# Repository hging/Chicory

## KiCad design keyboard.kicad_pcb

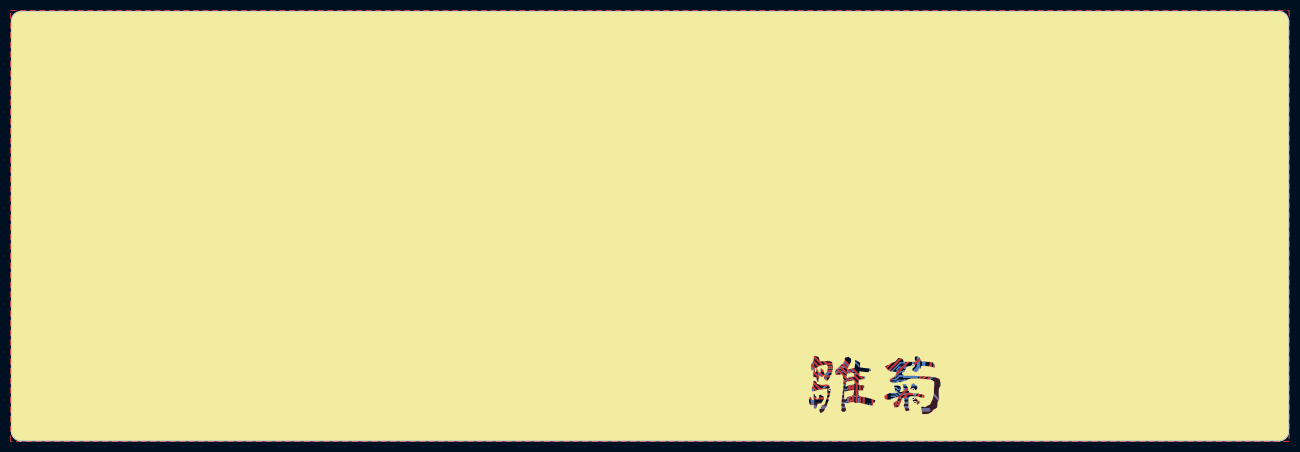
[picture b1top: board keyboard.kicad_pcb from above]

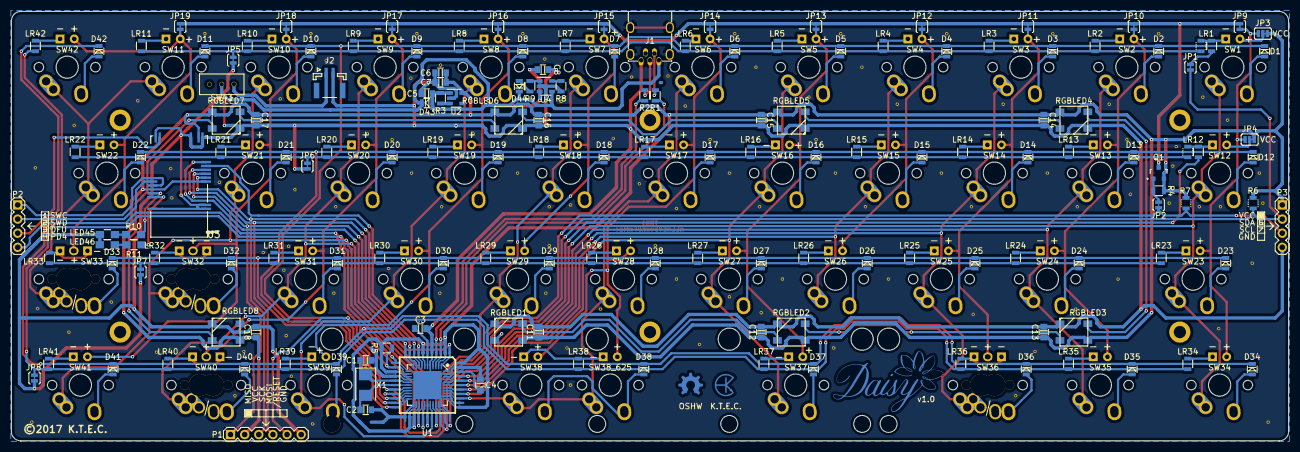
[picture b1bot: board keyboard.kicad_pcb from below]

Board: 2 copper layers, 229.6 x 77.2 mm, 349 parts (159 on the bottom side), 162 nets.

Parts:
C1, C2: 22pF; C_0805
C3: 1uF; C_0805
C4, C11, C12, C13, C14, C15, C16, C17, C18: 100nF; C_0805
C5, C6, C7, C8: 10uf; C_0805
D1, D2, D3, D4, D5, D6, D7, D8, D9, D10, D11, D12, D13, D14, D15, D16, D17, D18, D19, D20, D21, D22, D23, D24, D25, D26, D27, D28, D29, D30, D31, D32, D33, D34, D35, D36, D37, D38, D39, D40, D41, D42: DIODE; D_0805_V2
D43: D_Schottky_Small_ALT; D_0805_V2
D44: LED; D_0805_V2
J1: USB_MINI-B
J2: Conn_01x02; JST_GH_SM02B-GHS-TB_02x1.25mm_Angled
JP1, JP2, JP5, JP6, JP7, JP8, JP9, JP10, JP11, JP12, JP13, JP14, JP15, JP16, JP17, JP18, JP19: JUMPER; Jumper_SMD_2Pads_NC_V
JP3, JP4: JUMPER3; Jumper_SMD_3Pads_NC12
LED1, LED2, LED3, LED4, LED5, LED6, LED7, LED8, LED9, LED10, LED11, LED12, LED13, LED14, LED15, LED16, LED17, LED18, LED19, LED20, LED21, LED22, LED23, LED24, LED25, LED26, LED27, LED28, LED29, LED30, LED31, LED34, LED35, LED37, LED38, LED38_625, LED39, LED41, LED42: LED; MX1A_LED_Polar
LED32, LED33, LED36, LED40: LED; MX1A_LED_Polar_Dual
LED45, LED46: LED; R_0805_HandSoldering
LOGO1: Daisy_SilkS
LOGO2: Daisy_Logo
LOGO3: OSHW_LOGO; OSHW_Logo
LOGO4: KTEC_LOGO; KTEC_Logo
LR1, LR2, LR3, LR4, LR5, LR6, LR7, LR8, LR9, LR10, LR11, LR12, LR13, LR14, LR15, LR16, LR17, LR18, LR19, LR20, LR21, LR22, LR23, LR24, LR25, LR26, LR27, LR28, LR29, LR30, LR31, LR32, LR33, LR34, LR35, LR36, LR37, LR38, LR39, LR40, LR41, LR42: 330R; R_0805_V1
LR1-2, LR12-2: 330R; R_0805_NA
P1: ISP; Socket_Strip_Straight_1x06_Pitch2.54mm
P2: CONN_01X03; Socket_Strip_Straight_1x04_Pitch2.54mm
P3: GPIO_CLUSTER2; Socket_Strip_Straight_1x04_Pitch2.54mm
Q1: MOS_P; SOT-23
R1, R2: 22R; R_0805_V1
R3, R8: 100K; R_0805_V1
R4, R5: 10K; R_0805_V1
R6, R7: 4.7K; R_0805_NA
R9: 1K; R_0805_V1
R10, R11: 2.2K; R_0805_HandSoldering
RGBLED1, RGBLED2, RGBLED3, RGBLED4, RGBLED5, RGBLED6, RGBLED7, RGBLED8: WS2812B
SHIELD: Via_0.6mm
SHIELD#2, SHIELD#3, SHIELD#4, SHIELD#5, SHIELD#6, SHIELD#7, SHIELD#8, SHIELD#9, SHIELD#10, SHIELD#11, SHIELD#12, SHIELD#13, SHIELD#14, SHIELD#15, SHIELD#16, SHIELD#17, SHIELD#18, SHIELD#19, SHIELD#20, SHIELD#21, SHIELD#22, SHIELD#23, SHIELD#24, SHIELD#25, SHIELD#26, SHIELD#27, SHIELD#28, SHIELD#29, SHIELD#30, SHIELD#31, SHIELD#32, SHIELD#33, SHIELD#34, SHIELD#35, SHIELD#36, SHIELD#37, SHIELD#38, SHIELD#39, SHIELD#40, SHIELD#41, SHIELD#42, SHIELD#43, SHIELD#44, SHIELD#45, SHIELD#46, SHIELD#47, SHIELD#48, SHIELD#49, SHIELD#50, SHIELD#51, SHIELD#52, SHIELD#53, SHIELD#54, SHIELD#55, SHIELD#56, SHIELD#57, SHIELD#58, SHIELD#59, SHIELD#60, SHIELD#61, SHIELD#62, SHIELD#63, SHIELD#64, SHIELD#65, SHIELD#66, SHIELD#67, SHIELD#68, SHIELD#69, SHIELD#70, SHIELD#71, SHIELD#72, SHIELD#73, SHIELD#74, SHIELD#75, SHIELD#76, SHIELD#77, SHIELD#78, SHIELD#79, SHIELD#80, SHIELD#81, SHIELD#82, SHIELD#83, SHIELD#84, SHIELD#85, SHIELD#86, SHIELD#87, SHIELD#88, SHIELD#89, SHIELD#90, SHIELD#91, SHIELD#92, SHIELD#93, SHIELD#94, SHIELD#95, SHIELD#96, SHIELD#97, SHIELD#98, SHIELD#99, SHIELD#100, SHIELD#101, SHIELD#102, SHIELD#103: Via_0.6mm
SW1, SW2, SW3, SW4, SW5, SW6, SW7, SW8, SW9, SW10, SW11, SW13, SW14, SW15, SW16, SW17, SW18, SW19, SW20, SW21, SW24, SW25, SW26, SW27, SW28, SW29, SW30, SW31, SW35, SW39, SW42: MX1A; Mx_Alps_100_NoFSilk
SW12, SW34, SW41: MX1A; Mx_Alps_125_NoFSilk
SW22, SW23: MX1A; Mx_Alps_175_NoFSilk
SW32, SW33, SW36, SW40: MX1A; Mx_Alps_100_Dual_NoFSilk
SW37: MX1A; Mx_Alps_225_NoFSilk
SW38: MX1A; Mx_Alps_275_NoFSilk
SW38_625: MX1A; Mx_Alps_625_NoFSilk
SW43: DIP-TOGGLE-SWITCH(3P-9X3.5MM); toggle
U1: ATMEGA32U4; TQFP44+QFN44
U2: SPX3819M5-L-3-3; SOT-23-5
U3: MDBT40; ADA_MDBT40
U4: MCP73831; SOT-23-5
X1: CRYSTAL; Crystal_SMD_5032-2pin_5.0x3.2mm

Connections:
+BATT: C8.1, D43.2, SW43.2, U4.3
/Backlight: JP2.2, Q1.1, R4.2
/Caps: LR12.2, U1.31
/Col0: SW1.1, SW12.1, SW23.1, SW34.1, U1.41
/Col1: SW2.1, SW13.1, SW24.1, SW35.1, U1.40
/Col2: SW3.1, SW14.1, SW25.1, SW36.1, U1.39
/Col3: SW4.1, SW15.1, SW26.1, U1.38
/Col4: SW5.1, SW16.1, SW27.1, SW37.1, U1.37
/Col5: SW6.1, SW17.1, SW28.1, SW38.1, SW38_625.1, U1.36
/Col6: SW7.1, SW18.1, SW29.1, U1.30
/Col7: SW8.1, SW19.1, SW30.1, SW39.1, U1.29
/Col8: SW9.1, SW20.1, SW31.1, SW40.1, U1.28
/Col9: SW10.1, SW21.1, SW32.1, SW41.1, U1.27
/Col10: SW11.1, SW22.1, SW33.1, SW42.1, U1.26
/Esc: JP1.2, LR1.2
/GPIO0: U1.8, U3.7
/GPIO1: P1.3, U1.9, U3.4
/GPIO2: P1.4, U1.10, U3.6
/GPIO3: P1.1, U1.11, U3.5
/GPIO4: U1.1, U3.8
/GPIO5: P2.4, U1.25
/GPIO6: JP1.1, P3.2, R6.2, U1.19
/GPIO7: JP2.1, P3.3, R7.2, U1.18
/RGB: RGBLED1.4, U1.32
/Row0: D1.2, D2.2, D3.2, D4.2, D5.2, D6.2, D7.2, D8.2, D9.2, D10.2, D11.2, U1.20
/Row1: D12.2, D13.2, D14.2, D15.2, D16.2, D17.2, D18.2, D19.2, D20.2, D21.2, D22.2, U1.21
/Row2: D23.2, D24.2, D25.2, D26.2, D27.2, D28.2, D29.2, D30.2, D31.2, D32.2, D33.2, U1.22
/Row3: D34.2, D35.2, D36.2, D37.2, D38.2, D39.2, D40.2, D41.2, D42.2, U1.12
/SHIELD: J1.6, J1.7, J1.8, J1.9, SHIELD.1, SHIELD#2.1, SHIELD#3.1, SHIELD#4.1, SHIELD#5.1, SHIELD#6.1, SHIELD#7.1, SHIELD#8.1, SHIELD#9.1, SHIELD#10.1, SHIELD#11.1, SHIELD#12.1, SHIELD#13.1, SHIELD#14.1, SHIELD#15.1, SHIELD#16.1, SHIELD#17.1, SHIELD#18.1, SHIELD#19.1, SHIELD#20.1, SHIELD#21.1, SHIELD#22.1, SHIELD#23.1, SHIELD#24.1, SHIELD#25.1, SHIELD#26.1, SHIELD#27.1, SHIELD#28.1, SHIELD#29.1, SHIELD#30.1, SHIELD#31.1, SHIELD#32.1, SHIELD#33.1, SHIELD#34.1, SHIELD#35.1, SHIELD#36.1, SHIELD#37.1, SHIELD#38.1, SHIELD#39.1, SHIELD#40.1, SHIELD#41.1, SHIELD#42.1, SHIELD#43.1, SHIELD#44.1, SHIELD#45.1, SHIELD#46.1, SHIELD#47.1, SHIELD#48.1, SHIELD#49.1, SHIELD#50.1, SHIELD#51.1, SHIELD#52.1, SHIELD#53.1, SHIELD#54.1, SHIELD#55.1, SHIELD#56.1, SHIELD#57.1, SHIELD#59.1, SHIELD#60.1, SHIELD#61.1, SHIELD#62.1, SHIELD#63.1, SHIELD#64.1, SHIELD#65.1, SHIELD#66.1, SHIELD#67.1, SHIELD#68.1, SHIELD#69.1, SHIELD#70.1, SHIELD#71.1, SHIELD#72.1, SHIELD#73.1, SHIELD#74.1, SHIELD#75.1, SHIELD#76.1, SHIELD#77.1, SHIELD#78.1, SHIELD#79.1, SHIELD#80.1, SHIELD#81.1, SHIELD#82.1, SHIELD#83.1, SHIELD#84.1, SHIELD#85.1, SHIELD#86.1, SHIELD#87.1, SHIELD#88.1, SHIELD#89.1, SHIELD#90.1, SHIELD#91.1, SHIELD#92.1, SHIELD#93.1, SHIELD#94.1, SHIELD#95.1, SHIELD#96.1, SHIELD#97.1, SHIELD#98.1, SHIELD#99.1, SHIELD#100.1, SHIELD#101.1, SHIELD#102.1, SHIELD#103.1
/led/LCol0: JP3.3, JP4.3, JP9.2, LED23.1, LED34.1
/led/LCol1: JP10.2, LED2.1, LED13.1, LED24.1, LED35.1
/led/LCol2: JP11.2, LED3.1, LED14.1, LED25.1, LED36.1
/led/LCol3: JP12.2, LED4.1, LED15.1, LED26.1
/led/LCol4: JP13.2, LED5.1, LED16.1, LED27.1, LED37.1
/led/LCol5: JP14.2, LED6.1, LED17.1, LED28.1, LED38.1, LED38_625.1
/led/LCol6: JP15.2, LED7.1, LED18.1, LED29.1
/led/LCol7: JP16.2, LED8.1, LED19.1, LED30.1, LED39.1
/led/LCol8: JP17.2, LED9.1, LED20.1, LED31.1, LED40.1
/led/LCol9: JP18.2, LED10.1, LED21.1, LED32.1, LED41.1
/led/LCol10: JP19.2, LED11.1, LED22.1, LED33.1, LED42.1
/led/LRow0: JP5.2, LR1-2.2, LR2.2, LR3.2, LR4.2, LR5.2, LR6.2, LR7.2, LR8.2, LR9.2, LR10.2, LR11.2
/led/LRow1: JP6.2, LR12-2.2, LR13.2, LR14.2, LR15.2, LR16.2, LR17.2, LR18.2, LR19.2, LR20.2, LR21.2, LR22.2
/led/LRow2: JP7.2, LR23.2, LR24.2, LR25.2, LR26.2, LR27.2, LR28.2, LR29.2, LR30.2, LR31.2, LR32.2, LR33.2
/led/LRow3: JP8.2, LR34.2, LR35.2, LR36.2, LR37.2, LR38.2, LR39.2, LR40.2, LR41.2, LR42.2
/led/LVCC: JP9.1, JP10.1, JP11.1, JP12.1, JP13.1, JP14.1, JP15.1, JP16.1, JP17.1, JP18.1, JP19.1, Q1.3
/~RESET: P1.5, R5.2, U1.13
GND: C1.2, C2.2, C3.2, C4.2, C5.2, C6.2, C7.2, C8.2, C11.2, C12.2, C13.2, C14.2, C15.2, C16.2, C17.2, C18.2, J1.5, J2.2, JP5.1, JP6.1, JP7.1, JP8.1, LED45.1, LED46.1, P1.6, P3.4, R8.1, RGBLED1.3, RGBLED2.3, RGBLED3.3, RGBLED4.3, RGBLED5.3, RGBLED6.3, RGBLED7.3, RGBLED8.3, U1.0, U1.5, U1.15, U1.23, U1.33, U1.35, U1.43, U2.2, U3.1, U3.2, U3.13, U3.16, U3.25, U3.42, U4.2
unnamed: C1.1, U1.16, X1.1
unnamed: C2.1, U1.17, X1.2
unnamed: C3.1, U1.6
unnamed: C4.1, U1.42
unnamed: D1.1, SW1.2
unnamed: D2.1, SW2.2
unnamed: D3.1, SW3.2
unnamed: D4.1, SW4.2
unnamed: D5.1, SW5.2
unnamed: D6.1, SW6.2
unnamed: D7.1, SW7.2
unnamed: D8.1, SW8.2
unnamed: D9.1, SW9.2
unnamed: D10.1, SW10.2
unnamed: D11.1, SW11.2
unnamed: D12.1, SW12.2
unnamed: D13.1, SW13.2
unnamed: D14.1, SW14.2
unnamed: D15.1, SW15.2
unnamed: D16.1, SW16.2
unnamed: D17.1, SW17.2
unnamed: D18.1, SW18.2
unnamed: D19.1, SW19.2
unnamed: D20.1, SW20.2
unnamed: D21.1, SW21.2
unnamed: D22.1, SW22.2
unnamed: D23.1, SW23.2
unnamed: D24.1, SW24.2
unnamed: D25.1, SW25.2
unnamed: D26.1, SW26.2
unnamed: D27.1, SW27.2
unnamed: D28.1, SW28.2
unnamed: D29.1, SW29.2
unnamed: D30.1, SW30.2
unnamed: D31.1, SW31.2
unnamed: D32.1, SW32.2
unnamed: D33.1, SW33.2
unnamed: D34.1, SW34.2
unnamed: D35.1, SW35.2
unnamed: D36.1, SW36.2
unnamed: D37.1, SW37.2
unnamed: D38.1, SW38.2, SW38_625.2
unnamed: D39.1, SW39.2
unnamed: D40.1, SW40.2
unnamed: D41.1, SW41.2
unnamed: D42.1, SW42.2
unnamed: D44.1, R9.2
unnamed: J1.2, R1.2
unnamed: J1.3, R2.2
unnamed: J2.1, SW43.3
unnamed: JP3.2, LED1.1
unnamed: JP4.2, LED12.1
unnamed: LED1.2, LR1.1, LR1-2.1
unnamed: LED2.2, LR2.1
unnamed: LED3.2, LR3.1
unnamed: LED4.2, LR4.1
unnamed: LED5.2, LR5.1
unnamed: LED6.2, LR6.1
unnamed: LED7.2, LR7.1
unnamed: LED8.2, LR8.1
unnamed: LED9.2, LR9.1
unnamed: LED10.2, LR10.1
unnamed: LED11.2, LR11.1
unnamed: LED12.2, LR12.1, LR12-2.1
unnamed: LED13.2, LR13.1
unnamed: LED14.2, LR14.1
unnamed: LED15.2, LR15.1
unnamed: LED16.2, LR16.1
unnamed: LED17.2, LR17.1
unnamed: LED18.2, LR18.1
unnamed: LED19.2, LR19.1
unnamed: LED20.2, LR20.1
unnamed: LED21.2, LR21.1
unnamed: LED22.2, LR22.1
unnamed: LED23.2, LR23.1
unnamed: LED24.2, LR24.1
unnamed: LED25.2, LR25.1
unnamed: LED26.2, LR26.1
unnamed: LED27.2, LR27.1
unnamed: LED28.2, LR28.1
unnamed: LED29.2, LR29.1
unnamed: LED30.2, LR30.1
unnamed: LED31.2, LR31.1
unnamed: LED32.2, LR32.1
unnamed: LED33.2, LR33.1
unnamed: LED34.2, LR34.1
unnamed: LED35.2, LR35.1
unnamed: LED36.2, LR36.1
unnamed: LED37.2, LR37.1
unnamed: LED38.2, LED38_625.2, LR38.1
unnamed: LED39.2, LR39.1
unnamed: LED40.2, LR40.1
unnamed: LED41.2, LR41.1
unnamed: LED42.2, LR42.1
unnamed: LED45.2, R10.2
unnamed: LED46.2, R11.2
unnamed: P2.1, U3.36
unnamed: P2.2, U3.35
unnamed: P2.3, U3.24
unnamed: R1.1, U1.3
unnamed: R2.1, U1.4
unnamed: R3.1, U2.3
unnamed: R8.2, U4.5
unnamed: R9.1, U4.1
unnamed: R10.1, U3.38
unnamed: R11.1, U3.39
unnamed: RGBLED1.2, RGBLED2.4
unnamed: RGBLED2.2, RGBLED3.4
unnamed: RGBLED3.2, RGBLED4.4
unnamed: RGBLED4.2, RGBLED5.4
unnamed: RGBLED5.2, RGBLED6.4
unnamed: RGBLED6.2, RGBLED7.4
unnamed: RGBLED7.2, RGBLED8.4
VBUS: C5.1, D43.1, D44.2, J1.1, R3.2, U2.1, U4.4
VCC: C6.1, C7.1, C11.1, C12.1, C13.1, C14.1, C15.1, C16.1, C17.1, C18.1, JP3.1, JP4.1, P1.2, P3.1, Q1.2, R4.1, R5.1, R6.1, R7.1, RGBLED1.1, RGBLED2.1, RGBLED3.1, RGBLED4.1, RGBLED5.1, RGBLED6.1, RGBLED7.1, RGBLED8.1, U1.2, U1.7, U1.14, U1.24, U1.34, U1.44, U2.5, U3.3, U3.14

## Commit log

2017-10-29 Chicory init commit from Daisy
2017-10-29 2017年10月29日
2017-10-31 complete without ble led
2017-11-01 complete without bat switch
2017-11-05 v0.1 complete

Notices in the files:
keyboard.kicad_pcb:
©2017 K.T.E.C.
